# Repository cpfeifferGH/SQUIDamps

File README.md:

# SQUIDamps
Schematic and part list for the SQUIDamp amplifiers/filters described in my PhD thesis: On-scalp MEG using high-Tc SQUIDs - Measuring brain activity with superconducting magnetometers (ISBN 978-91-7905-173-0, Doktorsavhandlingar vid Chalmers tekniska högskola, Ny serie nr 4640, ISSN 0346-718X).

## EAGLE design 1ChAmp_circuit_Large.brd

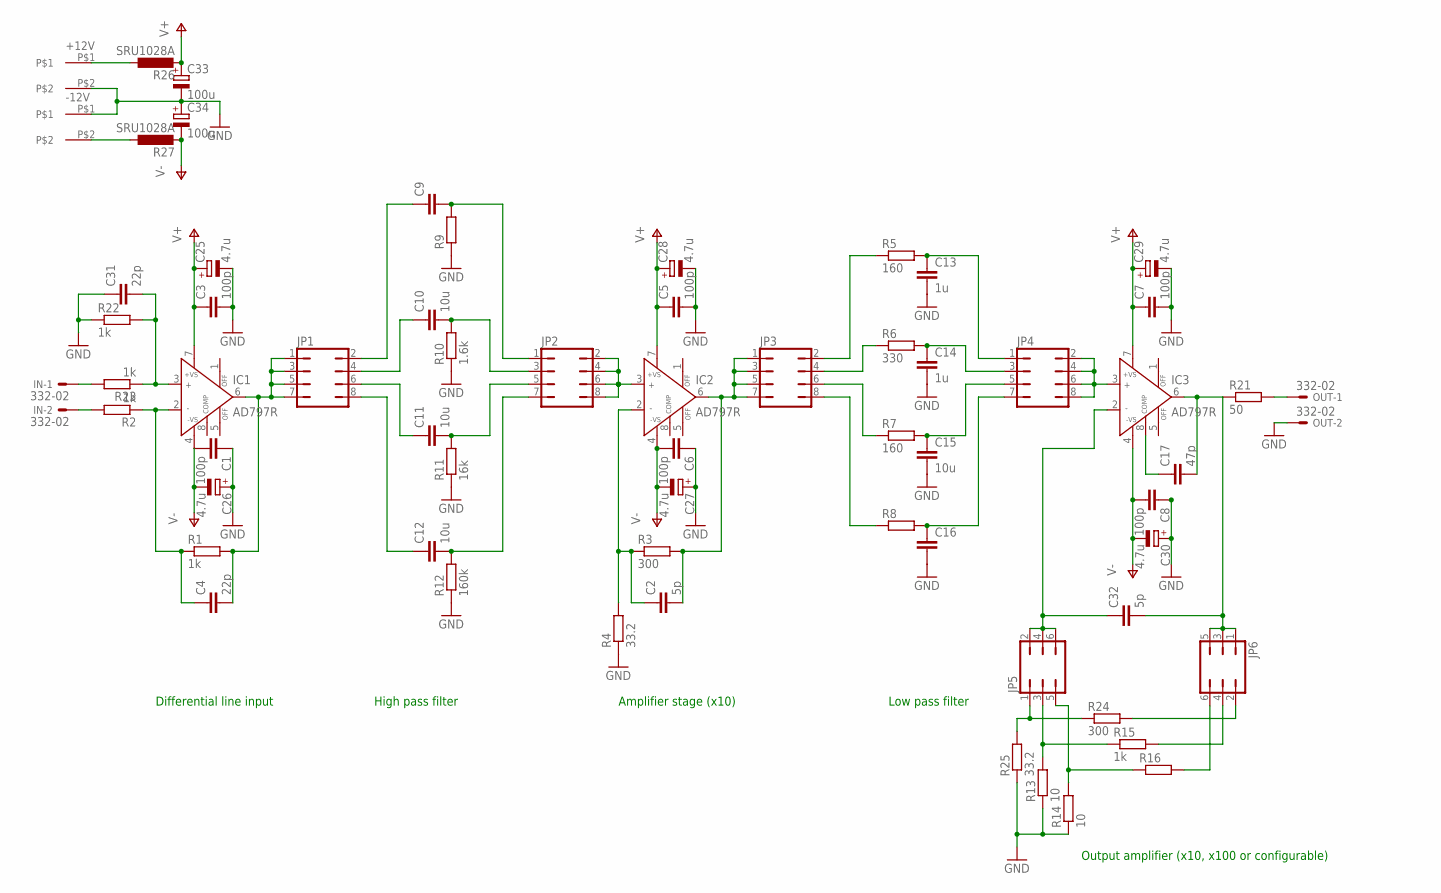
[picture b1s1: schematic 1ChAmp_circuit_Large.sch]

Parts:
+12V: B2P-VH
-12V: B2P-VH
C1, C3, C5, C6, C7, C8: 100p; C0805
C2, C32: 5p; C0805
C4, C31: 22p; C0805
C9, C16: C-EU025-025X050; C025-025X050
C10, C11, C12, C15: 10u; C0805
C13, C14: 1u; C0805
C17: 47p; C0805
C25, C26, C27, C28, C29, C30: 4.7u; C0805POL
C33, C34: 100u; C0805POL
IC1, IC2, IC3: AD797R; SO8
IN: 332-02
JP1, JP2, JP3, JP4: JP4Q
JP5, JP6: JP3Q
OUT: 332-02
R1, R2, R15, R22, R23: 1k; R0805
R3, R24: 300; R0805
R4, R25: 33.2; R0805
R5, R7: 160; R0805
R6: 330; R0805
R8, R9, R16: R-EU_0204/5; 0204/5
R10: 1.6k; R0805
R11: 16k; R0805
R12: 160k; R0805
R13, R14: 10; R0805
R21: 50; 0204/5
R26, R27: SRU1028A

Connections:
GND: +12V.P$2, -12V.P$1, C1.1, C3.2, C5.2, C6.1, C7.2, C8.1, C13.2, C14.2, C15.2, C16.2, C25.P$1 (-), C26.P$2 (+), C27.P$2 (+), C28.P$1 (-), C29.P$1 (-), C30.P$2 (+), C31.1, C33.P$1 (-), C34.P$2 (+), OUT.2, R4.1, R9.1, R10.1, R11.1, R12.1, R13.1, R14.1, R22.1, R25.1
unnamed: IN.2, R2.2
unnamed: OUT.1, R21.2
unnamed: IN.1, R23.2
unnamed: C31.2, IC1.3 (IN+), R22.2, R23.1
unnamed: JP5.5, R14.2, R16.1
unnamed: C13.1, JP4.1, R5.2
unnamed: C4.1, IC1.2 (IN-), R1.1, R2.1
unnamed: C4.2, IC1.6 (OUT), JP1.1, JP1.3, JP1.5, JP1.7, R1.2
unnamed: C2.1, IC2.2 (IN-), R3.1, R4.2
unnamed: C2.2, IC2.6 (OUT), JP3.1, JP3.3, JP3.5, JP3.7, R3.2
unnamed: C14.1, JP4.3, R6.2
unnamed: C17.1, IC3.8 (COMP)
unnamed: C15.1, JP4.5, R7.2
unnamed: C17.2, C32.2, IC3.6 (OUT), JP6.1, JP6.3, JP6.5, R21.1
unnamed: +12V.P$1, R26.P$1 (1)
unnamed: C16.1, JP4.7, R8.2
unnamed: JP5.3, R13.2, R15.1
unnamed: C9.2, JP2.1, R9.2
unnamed: JP5.1, R24.1, R25.2
unnamed: C10.2, JP2.3, R10.2
unnamed: JP6.2, R24.2
unnamed: C11.2, JP2.5, R11.2
unnamed: JP6.4, R15.2
unnamed: C12.2, JP2.7, R12.2
unnamed: JP6.6, R16.2
unnamed: C32.1, IC3.2 (IN-), JP5.2, JP5.4, JP5.6
unnamed: C9.1, JP1.2
unnamed: C10.1, JP1.4
unnamed: C11.1, JP1.6
unnamed: C12.1, JP1.8
unnamed: IC2.3 (IN+), JP2.2, JP2.4, JP2.6, JP2.8
unnamed: JP3.2, R5.1
unnamed: JP3.4, R6.1
unnamed: JP3.6, R7.1
unnamed: JP3.8, R8.1
unnamed: IC3.3 (IN+), JP4.2, JP4.4, JP4.6, JP4.8
unnamed: -12V.P$2, R27.P$1 (1)
V+: C3.1, C5.1, C7.1, C25.P$2 (+), C28.P$2 (+), C29.P$2 (+), C33.P$2 (+), IC1.7 (+VS), IC2.7 (+VS), IC3.7 (+VS), R26.P$2 (2)
V-: C1.2, C6.2, C8.2, C26.P$1 (-), C27.P$1 (-), C30.P$1 (-), C34.P$1 (-), IC1.4 (-VS), IC2.4 (-VS), IC3.4 (-VS), R27.P$2 (2)

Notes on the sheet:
Differential line input
High pass filter
Amplifier stage (x10)
Low pass filter
Output amplifier (x10, x100 or configurable)

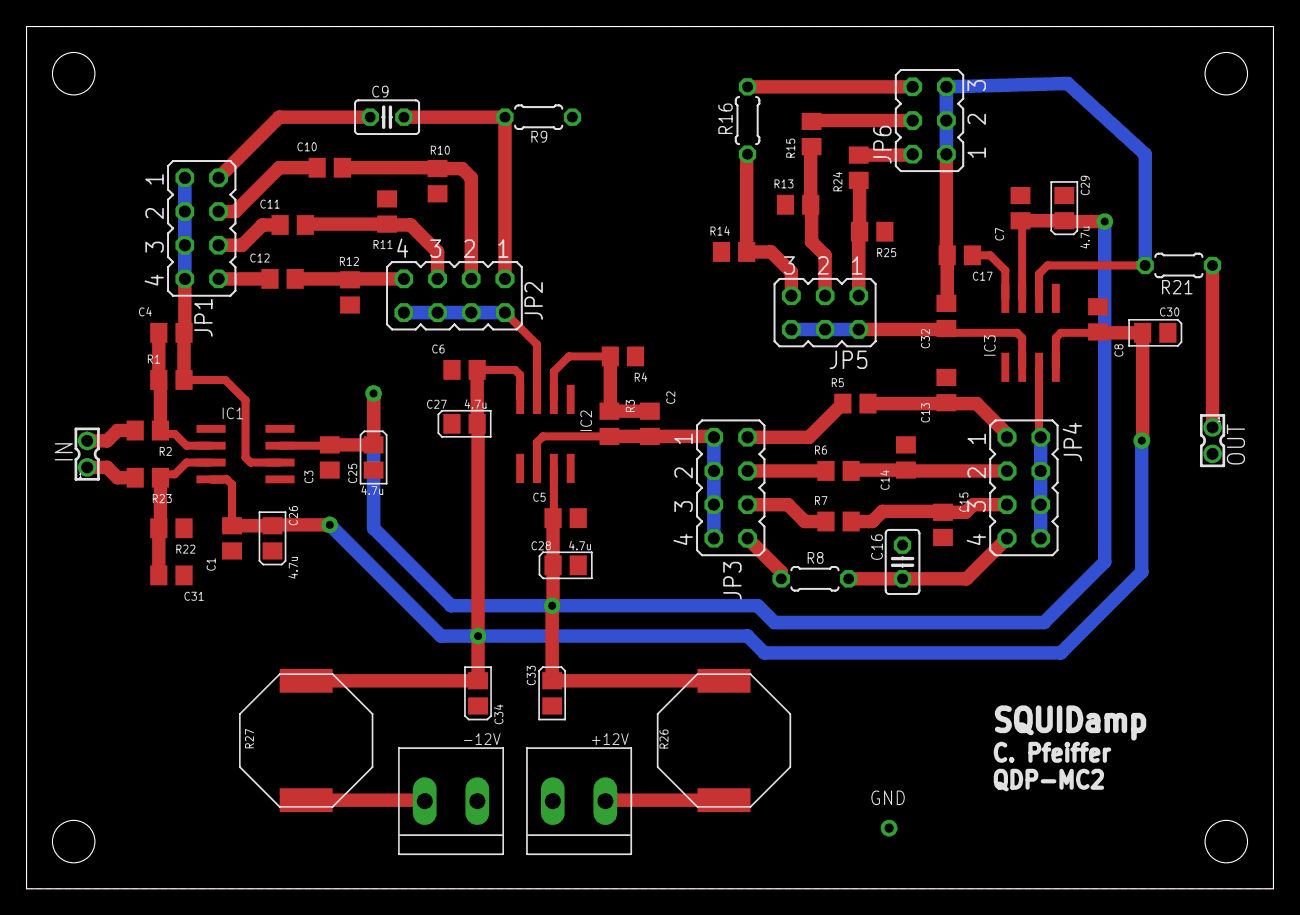
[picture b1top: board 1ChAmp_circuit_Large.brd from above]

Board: 2 copper layers, 94.0 x 65.0 mm, 63 parts (0 on the bottom side), 40 nets.

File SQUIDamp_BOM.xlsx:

Qty | Value | Device | Package | Parts | Description | MF | MPN | OC_FARNELL | OC_NEWARK | se.farnell | Price/1item | 7 | minQty | Total Price | Price/dev
2 |  | C-EU025-025X050 | C025-025X050 | C9, C16 | CAPACITOR, European symbol |  |  |  |  |  | 0 | 14 | 14 | 0 | 0
2 | 100u | CPOL-EUB45181A | B45181A | C33, C34 | POLARIZED CAPACITOR, European symbol |  |  | x |  | 1869995 | 41.24 | 14 | 14 | 577.36 | 82.48
2 |  | JP3Q | JP3Q | JP5, JP6 | JUMPER |  |  | x |  | 1022231 | 1.28 | 14 | 20 | 25.6 | 3.6571428571428575
4 |  | JP4Q | JP4Q | JP1, JP2, JP3, JP4 | JUMPER |  |  | x |  | 1022233 | 1.77 | 28 | 30 | 53.1 | 7.5857142857142863
4 |  | R-EU_0204/5 | 0204/5 | R8, R9, R16, R26, R27 | RESISTOR, European symbol |  |  |  |  |  | 0 | 28 | 28 | 0 | 0
2 | 12V | 22-23-2031 | B2+-VH(LF)(SN) | SUPPLY | JST 2pin B2P connector, 3.96mm |  |  | x |  | 9492003 | 1.05 | 14 | 15 | 15.75 | 2.25
1 | 1.6k | R-EU_R0805 | R0805 | R10 | RESISTOR, European symbol |  |  |  |  | 2670961 | 0.253 | 7 | 10 | 2.5300000000000002 | 0.36142857142857149
2 | 10 | R-EU_R0805 | R0805 | R13, R14 | RESISTOR, European symbol |  |  |  |  | 2670118 | 9.09 | 14 | 20 | 181.8 | 25.971428571428572
6 | 100p | C-EUC0805 | C0805 | C1, C3, C5, C6, C7, C8 | CAPACITOR, European symbol |  |  |  |  | 2320839 | 0.26400000000000001 | 42 | 50 | 13.200000000000001 | 1.8857142857142859
4 | 10u | C-EUC0805 | C0805 | C10, C11, C12, C15 | CAPACITOR, European symbol |  |  |  |  | 2320856 | 0.624 | 28 | 30 | 18.72 | 2.6742857142857139
2 | 160 | R-EU_R0805 | R0805 | R5, R7 | RESISTOR, European symbol |  |  |  |  | 2670960 | 0.26800000000000002 | 14 | 20 | 5.36 | 0.76571428571428579
1 | 160k | R-EU_R0805 | R0805 | R12 | RESISTOR, European symbol |  |  |  |  | 2670963 | 0.253 | 7 | 10 | 2.5300000000000002 | 0.36142857142857149
1 | 16k | R-EU_R0805 | R0805 | R11 | RESISTOR, European symbol |  |  |  |  | 2670962 | 0.26100000000000001 | 7 | 10 | 2.6100000000000003 | 0.37285714285714289
4 | 1k | R-EU_R0805 | R0805 | R1, R2, R15, R22, R23 | RESISTOR, European symbol |  |  |  |  | 2502670 | 0.19900000000000001 | 28 | 30 | 5.9700000000000006 | 0.85285714285714298
2 | 1u | C-EUC0805 | C0805 | C13, C14 | CAPACITOR, European symbol |  |  |  |  | 2320853 | 0.33800000000000002 | 14 | 15 | 5.07 | 0.72428571428571431
2 | 22p | C-EUC0805 | C0805 | C4, C31 | CAPACITOR, European symbol |  |  |  |  | 1759195 | 0.17499999999999999 | 14 | 20 | 3.5 | 0.5
2 | 300 | R-EU_R0805 | R0805 | R3, R24 | RESISTOR, European symbol |  |  |  |  | 2670223 | 9.3699999999999992 | 14 | 20 | 187.39999999999998 | 26.771428571428569
2 | 33.200000000000003 | R-EU_R0805 | R0805 | R4, R25 | RESISTOR, European symbol |  |  |  |  | 2670083 | 0.71799999999999997 | 14 | 20 | 14.36 | 2.0514285714285712
1 | 330 | R-EU_R0805 | R0805 | R6 | RESISTOR, European symbol |  |  |  |  | 2670238 | 9.3699999999999992 | 7 | 10 | 93.699999999999989 | 13.385714285714284
2 | 332-02 | 332-02 | 332-02 | IN, OUT | 2 Pin - 2mm Dual Row |  |  | x |  | 1593411 | 0.59399999999999997 | 14 | 14 | 8.3159999999999989 | 1.1879999999999999
6 | 4.7u | C-EUC0805 | C0805 | C25, C26, C27, C28, C29, C30 | CAPACITOR, European symbol |  |  |  |  | 1658237 | 5.93 | 42 | 45 | 266.84999999999997 | 38.121428571428567
1 | 47p | C-EUC0805 | C0805 | C17 | CAPACITOR, European symbol |  |  |  |  | 1759199 | 0.155 | 7 | 10 | 1.55 | 0.22142857142857145
1 | 50 | R-EU_0204/5 | 0204/5 | R21 | RESISTOR, European symbol |  |  | x |  | 1903694 | 2.71 | 7 | 7 | 18.97 | 2.71
2 | 5p | C-EUC0805 | C0805 | C2, C32 | CAPACITOR, European symbol |  |  |  |  | 1759184 | 0.34200000000000003 | 14 | 20 | 6.8400000000000007 | 0.9771428571428572
3 | AD797R | AD797R | SO8 | IC1, IC2, IC3 | Ultralow Distortion, Ultralow Noise Op Amp | ALTERA CORPORATION | AD797ARZ | x | 88H0085 | 9426450 | 98.09 | 21 | 21 | 2059.89 | 294.27
61 |  |  |  |  |  |  |  |  |  |  |  |  | SUM: | 3570.9759999999997 | 510.13942857142854
 |  |  |  |  |  |  |  |  |  | 9708391
